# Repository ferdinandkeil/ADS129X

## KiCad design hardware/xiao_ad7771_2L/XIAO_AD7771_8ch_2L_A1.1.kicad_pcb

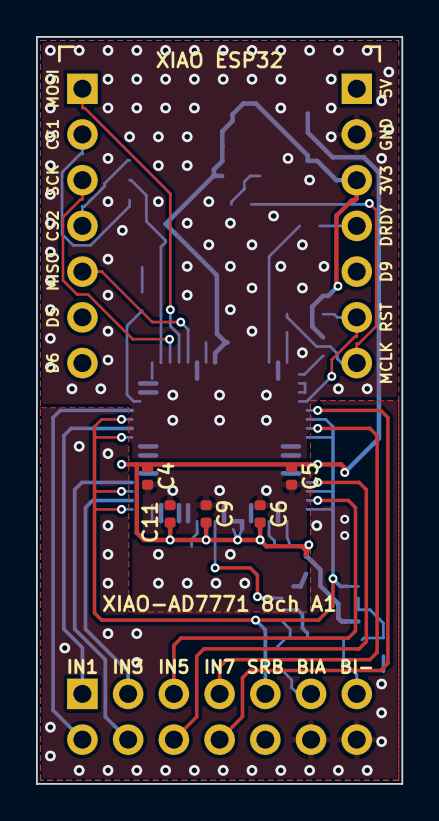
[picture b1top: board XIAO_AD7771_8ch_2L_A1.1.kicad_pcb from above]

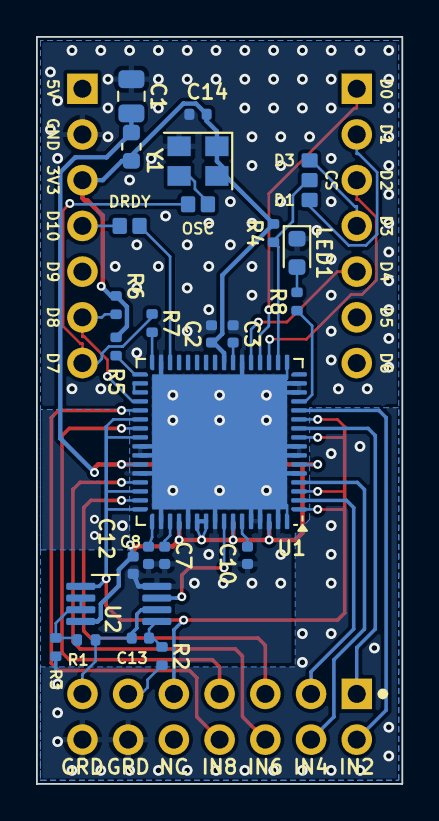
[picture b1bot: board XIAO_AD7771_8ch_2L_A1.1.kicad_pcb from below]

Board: 2 copper layers, 20.3 x 41.5 mm, 33 parts (26 on the bottom side), 38 nets.

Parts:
C1: 10u; C_0805_2012Metric
C2, C4, C5, C6, C8, C9, C11, C12: 100n; C_0402_1005Metric
C3, C7, C10: 1u; C_0402_1005Metric
C13: 270p C0G; C_0402_1005Metric
C14: 100n DNP; C_0402_1005Metric
FB1: 600R@100M; L_0603_1608Metric
J1: XIAO D0-D6; PinHeader_1x07_P2.54mm_Vertical
J2: XIAO 5V..D7; PinHeader_1x07_P2.54mm_Vertical
J3: Out 2x7 RA; PinHeader_2x07_P2.54mm_Horizontal
JP1: CS D1/D3; SJ3
JP2: DRDY; SJ2
JP3: OSC; SJ2
LED1: LED; LED_0603_1608Metric
R1: 1M; R_0402_1005Metric
R2: 100k; R_0402_1005Metric
R3: 4.7k; R_0402_1005Metric
R4, R5, R6: 10k; R_0402_1005Metric
R7: 47; R_0402_1005Metric
R8: 1k; R_0402_1005Metric
U1: AD7771BCPZ; QFN-64-1EP_9x9mm_P0.5mm_EP7.5x7.5mm
U2: OPA2333AIDGKR; MSOP-8_3x3mm_P0.65mm
Y1: 8MHz DNP; Oscillator_SMD_Abracon_ASE-4Pin_3.2x2.5mm

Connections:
3V3: C2.2, C14.1, FB1.2, J2.3, R4.1, R5.1, R6.1, U1.24, Y1.1, Y1.4
AREG1: C10.1, U1.59
AREG2: C7.1, U1.51
AVDD: C1.2, C4.1, C5.1, C6.2, C9.2, C11.2, C12.1, FB1.1, U1.6, U1.43, U1.52, U1.54, U1.55, U1.58, U1.62, U2.8
BIASINV: C13.2, J3.13, R1.1, U2.2
BIASOUT: J3.11, R2.2
BIAS_O: C13.1, R2.1, U2.1
CS: JP1.2, R4.2, U1.18
CS1: J1.2, JP1.1
CS2: J1.4, JP1.3
DRDY: JP2.1, U1.30
DRDYX: J2.4, JP2.2
DREG: C3.2, U1.23
GBUF: R1.2, R3.1, U2.6, U2.7
GND: C1.1, C2.1, C3.1, C4.2, C5.2, C6.1, C7.2, C8.2, C9.1, C10.2, C11.1, C12.2, C14.2, J2.2, LED1.1, U1.5, U1.7, U1.8, U1.14, U1.15, U1.17, U1.22, U1.31, U1.41, U1.42, U1.44, U1.50, U1.53, U1.56, U1.60, U1.61, U1.63, U1.64, U1.65, U2.4, Y1.2
GPIO0: R8.2, U1.13
GUARD: J3.12, J3.14, R3.2
IN1: J3.1, U1.10
IN2: J3.2, U1.12
IN3: J3.3, U1.2
IN4: J3.4, U1.4
IN5: J3.5, U1.47
IN6: J3.6, U1.45
IN7: J3.7, U1.39
IN8: J3.8, U1.37
LED_A: LED1.2, R8.1
MCLK: J2.7, JP3.2, R7.1
MCLK_U: R7.2, U1.32
MISO: J1.5, U1.21
MOSI: J1.1, U1.20
OSC: JP3.1, Y1.3
REF: C8.1, U1.49
RESET: J2.6, R6.2, U1.36
SCK: J1.3, U1.19
SRB: J3.9, U1.1, U1.3, U1.9, U1.11, U1.38, U1.40, U1.46, U1.48, U2.5
START: R5.2, U1.33
SYNC: U1.34, U1.35
VCM: U1.57, U2.3

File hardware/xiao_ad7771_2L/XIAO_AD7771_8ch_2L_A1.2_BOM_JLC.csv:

Comment,Designator,Footprint,LCSC Part #
10u,C1,0805,
100n,"C2,C8,C12",0402,
1u,"C3,C7,C10",0402,
100n,"C4,C5,C6,C9,C11",0402,
270p C0G,C13,0402,
600R@100M,FB1,0603,
LED,LED1,LED_0603_1608Metric,
1M,R1,0402,
100k,R2,0402,
4.7k,R3,0402,
10k,"R4,R5,R6",0402,
47,R7,0402,
1k,R8,0402,
AD7771BCPZ,U1,QFN-64-1EP_9x9mm_P0.5mm_EP7.5x7.5mm,
OPA2333AIDGKR,U2,MSOP-8_3x3mm_P0.65mm,

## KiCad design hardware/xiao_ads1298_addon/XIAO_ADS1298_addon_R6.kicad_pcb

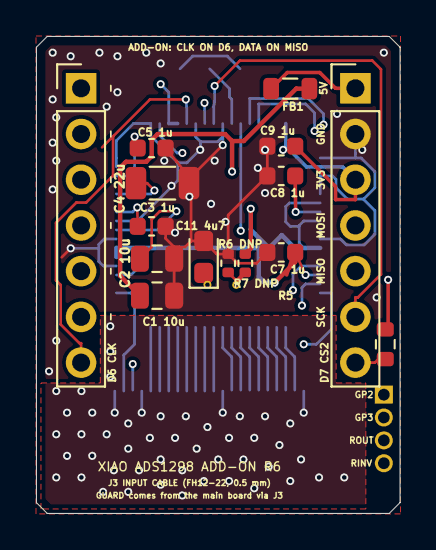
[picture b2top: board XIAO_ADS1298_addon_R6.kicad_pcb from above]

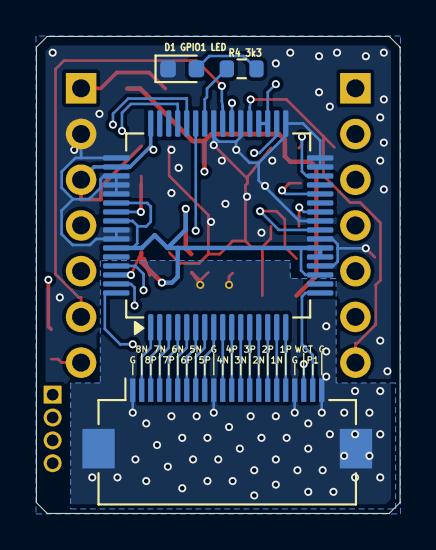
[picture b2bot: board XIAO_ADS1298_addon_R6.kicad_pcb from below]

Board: 4 copper layers, 20.2 x 26.5 mm, 22 parts (5 on the bottom side), 39 nets.

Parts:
C1, C2: 10u; C_0805_2012Metric
C3, C5, C7, C8, C9: 1u; C_0603_1608Metric
C4: 22uF 6.3V; C_1206_3216Metric
C11: 4.7u 10V tant; CP_EIA-2012-12_Kemet-R
D1: LED; LED_0603_1608Metric
FB1: 600R@100MHz; L_0805_2012Metric
GV1, GV2: guard via; GuardVia
J1: XIAO left (pass-through); PinHeader_1x07_P2.54mm_Vertical
J2: XIAO right (pass-through); PinHeader_1x07_P2.54mm_Vertical
J3: FH12-22S-0.5SH(55); Hirose_FH12-22S-0.5SH_1x22-1MP_P0.50mm_Horizontal
J4: 1x4 1.27mm; PinHeader_1x04_P1.27mm_Vertical
R4: 3.3k; R_0603_1608Metric
R5: 10k; R_0603_1608Metric
R6, R7: 200k; R_0402_1005Metric
U1: ADS1298IPAG; TQFP-64_10x10mm_P0.5mm

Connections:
+5V: FB1.1, J2.1
AVDD: C1.1, C7.1, FB1.2, R6.2, U1.19, U1.21, U1.22, U1.54, U1.56, U1.59, U1.62
CLK: J1.7, U1.37
CS2: J2.7, R5.2, U1.39
DVDD: C9.1, J2.3, R5.1, U1.35, U1.36, U1.48, U1.50
GND: C1.2, C2.2, C3.2, C4.2, C5.2, C7.2, C8.2, C9.2, C11.2, D1.1, J2.2, R7.2, U1.20, U1.23, U1.25, U1.31, U1.32, U1.33, U1.38, U1.41, U1.49, U1.51, U1.52, U1.53, U1.57, U1.58
GPIO1: R4.1, U1.42
GPIO2: J4.1, U1.44
GPIO3: J4.2, U1.45
GUARD: C11.1, GV1.1, GV2.1, J3.1, J3.10, J3.19, J3.22, J3.MP, R6.1, R7.1
IN1N: J3.17, U1.15
IN1P: J3.18, U1.16
IN2N: J3.15, U1.13
IN2P: J3.16, U1.14
IN3N: J3.13, U1.11
IN3P: J3.14, U1.12
IN4N: J3.11, U1.9
IN4P: J3.12, U1.10
IN5N: J3.8, U1.7
IN5P: J3.9, U1.8
IN6N: J3.6, U1.5
IN6P: J3.7, U1.6
IN7N: J3.4, U1.3
IN7P: J3.5, U1.4
IN8N: J3.2, U1.1
IN8P: J3.3, U1.2
LED_A: D1.2, R4.2
MISO: J2.5, U1.43
MOSI: J2.4, U1.34
PACE1: J3.21, U1.17
RLDINV: J4.4, U1.61
RLDOUT: J4.3, U1.63
SCK: J2.6, U1.40
VCAP1: C4.1, U1.28
VCAP2: C5.1, U1.30
VCAP3: C8.1, U1.55
VCAP4: C3.1, U1.26
VREFP: C2.1, U1.24
WCT: J3.20, U1.64

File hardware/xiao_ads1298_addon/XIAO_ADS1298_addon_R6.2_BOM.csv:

Refs,Qty,Value / part,Footprint,Side
C1 C2,2,10u,C_0805_2012Metric,Top
C3 C5 C7 C8 C9,5,1u,C_0603_1608Metric,Top
C4,1,22uF 6.3V,C_1206_3216Metric,Top
C11,1,4.7u 10V tant,CP_EIA-2012-12_Kemet-R,Top
D1,1,LED,LED_0603_1608Metric,Bottom
FB1,1,600R@100MHz,L_0805_2012Metric,Top
J1,1,XIAO left (pass-through),PinHeader_1x07_P2.54mm_Vertical,Top
J2,1,XIAO right (pass-through),PinHeader_1x07_P2.54mm_Vertical,Top
J3,1,FH12-18S-0.5SH(55),Hirose_FH12-18S-0.5SH_1x18-1MP_P0.50mm_Horizontal,Bottom
J4,1,2x3 1.27mm,PinHeader_2x03_P1.27mm_Vertical,Bottom
R4,1,3.3k,R_0603_1608Metric,Bottom
R5,1,10k,R_0603_1608Metric,Top
R6 R7,2,200k,R_0402_1005Metric,Top
U1,1,ADS1298IPAG,TQFP-64_10x10mm_P0.5mm,Bottom

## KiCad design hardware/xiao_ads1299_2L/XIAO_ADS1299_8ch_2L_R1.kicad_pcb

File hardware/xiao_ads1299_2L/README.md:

# XIAO-ADS1299 8-channel shield, 2-layer, R2.3 (stackable to two boards)

**R2.3** re-lays the top half so SPI uses the XIAO's standard SPI pins (D8–D10). On the XIAO nRF54L15 these are the fixed pins of SPIM00, its high-speed SPI; ESP32 boards can remap SPI, but the nRF54L15 can't. D4/D5 (I²C) and D2 stay free and pass straight through the stacking headers to a sensor board.

| XIAO pin | nRF54L15 | R2.3 | R2.2 |
|---|---|---|---|
| D0 | P1.04 | DRDY (JP4) | MOSI |
| D1 | P1.05 | shared ADS clock (JP2) | CS, board 1 |
| D2 | P1.06 | free (PPG_INT on a sensor board) | SCK |
| D3 | P1.07 | CS, board 1 (JP1) | CS, board 2 |
| D4 / D5 | P1.10 / P1.11 | free: I²C pass-through | shared clock / free |
| D6 | P2.08 | free | free |
| D7 | P2.07 | CS, board 2 (JP5) | free |
| D8 | P2.01 | SCK | free |
| D9 | P2.04 | MISO | MISO |
| D10 | P2.02 | MOSI | DRDY |

This is the same pin map as the 4-layer main R5.2 / add-on R6.2 boards, so one firmware build serves both.

**Other R2.3 changes:**
- **CS jumpers:** the 3-pad JP1 is now two 2-pad jumpers in the top corners: JP1 (marked 1) sends CS to D3 and JP5 (marked 2) sends it to D7. CS runs along the top edge to both.
- **Jumper positions:** JP2 (CLK) and JP4 (DRDY) sit next to D1/D0.
- **R1 (CS pull-up)** is on the bottom side, top-left; R4 (LED resistor) is on the top side.
- **LED:** D1 is driven by **GPIO4** (pin 46) and is **active-low**: its anode is on DVDD, so writing GPIO4 low turns it on. GPIO1's pin sits between SCK and MISO with no room for a via.
- **Power:** AVDD comes from the 5 V pin on the bottom layer through the empty corner beside the chip, then down the inside of J2. DVDD comes straight from the 3V3 pin into pin 50, as before.
- **SRB2** no longer crosses the input area. On the top side it runs from its via beside pin 18 straight across at the via's level, then in one 45° diagonal down to J3 between pins 9 and 11, and into pin 10. The top-side guard under the input header pins is one solid pour.
- **Ground fill:** every ground pocket cut off by the SPI, CS and power traces (around 3V3/MOSI/MISO/SCK/CS2 on top, D7–D9 on the bottom, between DRDY and MOSI at the top) is kept and stitched to ground on the other layer with its own via, 7 in all. Only slivers under 2 mm² stay empty, where no via fits.
- **Decoupling, under-chip fan-out and inputs:** unchanged from R2.2, apart from C4 moving 0.4 mm left and C9 0.05 mm up.

The design-rule report has no clearance errors and nothing unconnected, `tools/check_via_in_pad.py` finds no via in any part pad, and every trace is straight or at 45°. The only notes are library-footprint notes and the solder-jumper outlines trimmed at their own pads.

**XIAO nRF54L15 firmware:** use `&spi00` (Zephyr's `xiao_spi`) on D8–D10, DRDY on D0 as an interrupt (P1 supports it; P2 GPIOs don't), and disable `uart21` when a second board uses D7 as CS: `&uart21 { status = "disabled"; };`.

**R2.2 changes from R2.1:** C8 became 0402 and its ground via moved out of its pad.

**R2.1 changes from R2:** guard filter only. Copper routing is unchanged.
- **R3** is now **100 kΩ** (was 4.7 kΩ).
- **C10 (new):** 2.2 µF X7R 0603 from GUARD to GND, on the top side at the edge of the guard pour.

Together, R3 and C10 form a low-pass filter with its corner at about 0.7 Hz. The guard keeps the body's DC level but no longer carries the bias drive's correction signal, which moves opposite to the inputs. At AC it now behaves like a quiet shield. The capacitor sits on the guard side of R3, so the ADS1299 bias amplifier never sees it directly. After power-up or an electrode reconnect, the guard takes a few seconds to settle.

DRC is clean. There are no unconnected pads, and the only notes are library-footprint notes.

R2 is the R1 board plus four open solder jumpers, so two boards can share one XIAO with a common clock, and a 2×7 output header that adds BIASINV and a second GUARD pin. The board is still 20.0 × 25.8 mm, 2 layers. Every square trace corner is chamfered with a small 45°; the only remaining right angles are T-junctions and trace entries into pads or vias. DRC is clean (0.15 mm clearance, 0.6/0.3 mm vias, 0.6 mm minimum silkscreen text).

## Output header J3 (2×7, 2.54 mm, right angle)

Odd pins are on the inner row and even pins on the outer row. Pin 1 is marked with a dot on the ADS side.

| Column | Inner row | Outer row |
|---|---|---|
| 1 | 1 IN1P | 2 IN2P |
| 2 | 3 IN3P | 4 IN4P |
| 3 | 5 IN5P | 6 IN6P |
| 4 | 7 IN7P | 8 IN8P |
| 5 | 9 SRB1 | 10 SRB2 |
| 6 | 11 BIASOUT | 12 GUARD |
| 7 | 13 BIASINV | 14 GUARD |

- **Pins 9–12 changed from R1.** SRB2 moved to pin 10, BIASOUT to pin 11 and GUARD to pin 12. Pins 13 (BIASINV) and 14 (GUARD) are the new outer column.
- **Splitting the header:** a 2×6 right-angle header on pins 1–12 plus a 1×2 right-angle on pins 13/14 fits the same holes. The 1×2 is the board-to-board link: BIASINV and GUARD.
- **Silkscreen names (ADS side, above row 1 and below row 2):** IN1–IN8; SR1/SR2 = SRB1/SRB2; BIA = BIASOUT; BI- = BIASINV; GRD = GUARD.

## Solder jumpers (top side, all ship open)

| Jumper | Silkscreen | Bridge | Effect |
|---|---|---|---|
| JP1 | 1 (top-left corner) | bridge | chip select on D3 (board 1, or a single board) |
| JP5 | 2 (top-right corner) | bridge | chip select on D7 (board 2) |
| JP4 | DRDY | bridge | DRDY to D0. Board 1 or a single board only; leave open on board 2 |
| JP2 | CLK | bridge | ADS1299 CLK pin to D1, the shared clock line. Bridge on both boards of a stack; leave open on a single board |
| JP3 | EXT | bridge | CLKSEL to ground: external clock. Board 2 only. R5 (10 kΩ) holds CLKSEL high otherwise |

| Setup | JP1 | JP5 | JP4 | JP2 | JP3 |
|---|---|---|---|---|---|
| Single board | bridged (D3) | open | bridged | open | open |
| Stack, board 1 (clock master) | bridged (D3) | open | bridged | bridged | open |
| Stack, board 2 | open | bridged (D7) | open | bridged | bridged |

- **Board 1 firmware:** set CLK_EN in CONFIG1 so board 1 drives its 2.048 MHz clock onto D1.
- **Starting both boards together:** pull both CS lines low and send START (or SYNC). The two boards then convert in lockstep, and board 1's DRDY times both. Read board 1, then board 2, on the shared SPI bus.
- **Don't drive D1 from the XIAO:** leave it as an input.

## Second board in a stack

- **Leave off R2, C9 and R3.** C10 is optional on board 2: fitted, it just adds to the shared guard capacitance. Then only board 1's feedback network is on the shared BIASINV line, and board 2's guard comes only from board 1 over pin 14.
- **Firmware:** power down board 2's bias amplifier (PD_BIAS = 0 in CONFIG3). Its BIAS_SENSP/N channels still sum into board 1's amplifier through the shared BIASINV, as the ADS1299 datasheet shows for multiple devices.
- **Wiring:** link pins 13 and 14 between the boards, and make sure both boards' SRB1 lines reach the same reference electrode.
- **Stacking headers:** J1/J2 on the lower board need long-tail stacking headers so the XIAO pins pass through.

## XIAO pin use

| XIAO pin | ESP32-S3 GPIO | nRF54L15 | Signal |
|---|---|---|---|
| D0 | GPIO1 | P1.04 | DRDY (JP4) |
| D1 | GPIO2 | P1.05 | shared ADS clock (JP2) |
| D3 | GPIO4 | P1.07 | CS, board 1 (JP1) |
| D7 | GPIO44 | P2.07 | CS, board 2 (JP5) |
| D8 | GPIO7 | P2.01 | SCK |
| D9 | GPIO8 | P2.04 | MISO (ADS DOUT) |
| D10 | GPIO9 | P2.02 | MOSI (ADS DIN) |
| D2, D4, D5, D6 | | | not used; pass through the stacking headers (D4/D5 = I²C) |
| 5V | n/a | n/a | AVDD (ADS analog 5 V) |
| 3V3 | n/a | n/a | DVDD |
| GND | n/a | n/a | GND |

- **CS pull-up:** R1 (10 kΩ) sits on the ADS side of the CS jumpers, so an unbridged chip stays deselected.
- **Arduino setup:** `SPI.begin(D8 /*SCK*/, D9 /*MISO*/, D10 /*MOSI*/)`, mode 1, with CS on D3 and D7 handled in code.
- **Power note:** AVDD comes from the XIAO's 5V pin. That pin is live only on USB, or when 5 V is fed into it.

## Inputs, reference, guard

These are unchanged from R1, apart from routing.

- **Negative inputs:** all eight are tied to SRB1 on the board.
- **Positive inputs:** they run on the bottom layer with one 45° jog and no vias, under guard copper on both layers.
- **SRB2:** it runs on the top layer from a via beside pin 18, in one 45° diagonal to J3 between pins 9 and 11, and into pin 10.
- **BIASINV:** it runs on the top layer inside the guard pour to pin 13.
- **Guard:** it is fed from BIASOUT through R3 (100 kΩ), filtered by C10 (2.2 µF) to ground, and stitched with 16 vias.
- **Ground:** it is stitched with 17 vias.

## Bias

R2 (1 MΩ) in parallel with C9 (1.5 nF C0G) sits between BIASINV and BIASOUT. The corner is about 106 Hz.

## ADS1299 fixed pins

| Pin | Connection |
|---|---|
| CLKSEL | R5 (10 kΩ) to DVDD; JP3 to ground for an external clock |
| CLK | JP2 to D1 |
| START | low (use the START command) |
| RESET, PWDN | high |
| DAISY_IN, RESV1 | ground |
| GPIO4 | LED D1 through R4 (3.3 kΩ), active-low (anode on DVDD) |
| GPIO1–3 | not connected |

## Assembly

- **Top side (XIAO side):** C1–C10, R2–R5. Bridge the jumpers for your setup (see the table above).
- **Bottom side (ADS side):** U1, D1, R1, then J3.
- **Sockets:** J1/J2 go on last, as long-tail stacking headers on the lower board of a stack.

## Files

| File | Contents |
|---|---|
| `XIAO_ADS1299_8ch_2L_R2.3.kicad_pcb` / `.kicad_pro` | KiCad 7 board and rules |
| `XIAO_ADS1299_8ch_2L_R2.3` gerber/ | Gerbers and drill file |
| `XIAO_ADS1299_8ch_2L_R2.3_BOM.csv` | Bill of materials, with notes for the 2nd board |
| `plots/*_top_bottom.png`, `*_layers.png`, `*_via_check.png` | Both sides, copper by net, via check |

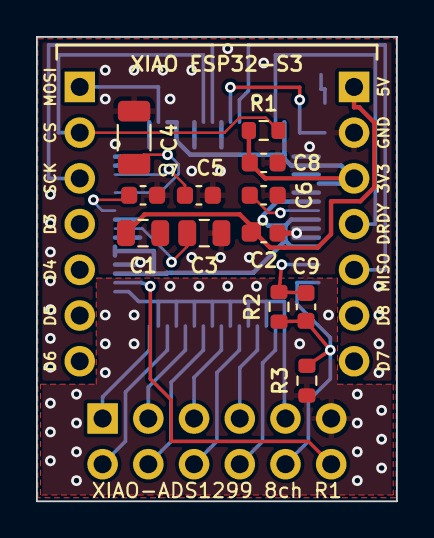
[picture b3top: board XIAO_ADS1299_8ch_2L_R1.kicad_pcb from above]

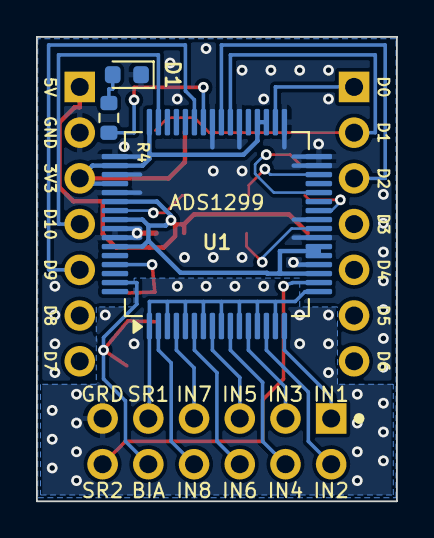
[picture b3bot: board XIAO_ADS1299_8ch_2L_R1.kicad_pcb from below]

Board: 2 copper layers, 20.0 x 25.8 mm, 18 parts (4 on the bottom side), 28 nets.

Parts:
C1, C3: 10u; C_0805_2012Metric
C2, C5, C6, C7, C8: 1u; C_0603_1608Metric
C4: 100u; C_1206_3216Metric
C9: 1.5n C0G; C_0603_1608Metric
D1: LED; LED_0603_1608Metric
J1: XIAO D0-D6; PinHeader_1x07_P2.54mm_Vertical
J2: XIAO 5V..D7; PinHeader_1x07_P2.54mm_Vertical
J3: Out 2x6 RA; PinHeader_2x06_P2.54mm_Horizontal
R1: 10k; R_0603_1608Metric
R2: 1M; R_0603_1608Metric
R3: 4.7k; R_0603_1608Metric
R4: 3.3k; R_0603_1608Metric
U1: ADS1299IPAG; TQFP-64_10x10mm_P0.5mm

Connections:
AVDD: C1.1, C2.1, J2.1, U1.19, U1.21, U1.22, U1.54, U1.56, U1.59
BIASINV: C9.1, R2.1, U1.61
BIASOUT: C9.2, J3.10, R2.2, R3.1, U1.63
CS: J1.2, R1.2, U1.39
DRDY: J2.4, U1.47
DVDD: C8.1, J2.3, R1.1, U1.35, U1.36, U1.48, U1.50, U1.52
GND: C1.2, C2.2, C3.2, C4.2, C5.2, C6.2, C7.2, C8.2, D1.1, J2.2, U1.20, U1.23, U1.25, U1.31, U1.32, U1.33, U1.38, U1.41, U1.49, U1.51, U1.53, U1.57, U1.58
GPIO1: R4.1, U1.42
GUARD: J3.11, R3.2
IN1P: J3.1, U1.16
IN2P: J3.2, U1.14
IN3P: J3.3, U1.12
IN4P: J3.4, U1.10
IN5P: J3.5, U1.8
IN6P: J3.6, U1.6
IN7P: J3.7, U1.4
IN8P: J3.8, U1.2
LED_A: D1.2, R4.2
MISO: J2.5, U1.43
MOSI: J1.1, U1.34
SCK: J1.3, U1.40
SRB1: J3.9, U1.1, U1.3, U1.5, U1.7, U1.9, U1.11, U1.13, U1.15, U1.17
SRB2: J3.12, U1.18
VCAP1: C4.1, U1.28
VCAP2: C5.1, U1.30
VCAP3: C6.1, U1.55
VCAP4: C7.1, U1.26
VREFP: C3.1, U1.24

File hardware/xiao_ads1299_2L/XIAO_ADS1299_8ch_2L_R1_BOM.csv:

Refs,Qty,Value / part,Footprint,Side
C1 C3,2,10u,C_0805_2012Metric,Top (XIAO side)
C2 C5 C6 C7 C8,5,1u,C_0603_1608Metric,Top (XIAO side)
C4,1,100u,C_1206_3216Metric,Top (XIAO side)
C9,1,1.5 nF C0G 0603,C_0603_1608Metric,Top (XIAO side)
D1,1,LED 0603,LED_0603_1608Metric,Bottom (ADS side)
J1,1,1x7 2.54 mm socket/header for XIAO (D0-D6),PinHeader_1x07_P2.54mm_Vertical,Top (XIAO side)
J2,1,1x7 2.54 mm socket/header for XIAO (5V..D7),PinHeader_1x07_P2.54mm_Vertical,Top (XIAO side)
J3,1,2x6 2.54 mm right-angle pin header,PinHeader_2x06_P2.54mm_Horizontal,Bottom (ADS side)
R1,1,10k,R_0603_1608Metric,Top (XIAO side)
R2,1,1M,R_0603_1608Metric,Top (XIAO side)
R3,1,4.7k,R_0603_1608Metric,Top (XIAO side)
R4,1,3.3k,R_0603_1608Metric,Bottom (ADS side)
U1,1,ADS1299IPAG (TQFP-64); ADS1299-6 also fits,TQFP-64_10x10mm_P0.5mm,Bottom (ADS side)
